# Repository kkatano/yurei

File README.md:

# Yurei
A Tenkeyless PCB inspired by Phantom

## Features
 * QMK Firmware
 * Teensy 2.0 controller
 * Minimal layout support
 * No switch LEDs and no underglow
 * All switches are south facing
 * Compatible with Filco Majestouch 2 case
 * Designed with KiCAD 5.1.4

## Supported Layouts
 * ANSI

## Supported Switches
 * Cherry MX and Cherry MX style switches

## Supported Cases
 * Filco Majestouch 2

### Note
 * [A bit modification to Filco case](images/bottom-case-mod.png) is required to install the USB cable.
 * Some other keyboard cases may also be compatible, but they have not been tested.
 * [YMDK aluminum case is not compatible](images/filco-pcb-and-ymdk-case-problem.pdf) (almost good but plate and pcb are slightly too thick, so that it causes a gap between the top and bottom cases).
   * Genuine filco PCBs and phantom PCBs also have the same problem.
   * I'm designing a new concept PCB named [Wallaby](https://github.com/kkatano/wallaby) to solve this problem. 

## BOM

| Reference | Description | Value     |URL                                                                                                      | Qty | 
|-----------|-------------|-----------|---------------------------------------------------------------------------------------------------------|-----| 
| D1-D87    | Diode       | 1N4148    |https://www.digikey.jp/product-detail/en/on-semiconductor/1N4148/1N4148FS-ND/458603                      | 87  | 
| L1, L2    | LED         | LED       |https://www.digikey.jp/product-detail/en/vishay-semiconductor-opto-division/VLHW4100/751-1502-ND/2403143 | 2   | 
| R1, R2    | Resistor    | 10k       |https://www.digikey.jp/product-detail/en/yageo/MFR-25FBF52-10K/10.0KXBK-ND/13219                         | 2   | 
| SW1-SW87  | Key switch  | Cherry MX |                                                                                                         | 87  | 
| U1        | Controller  | Teensy2.0 |https://www.pjrc.com/store/teensy.html                                                                   | 1   | 

You also need following parts to build keyboard.

 * [LED spacer](https://www.digikey.jp/product-detail/en/keystone-electronics/7362/36-7362-ND/316720)
   * 2 pieces
 * Stabilizers
   * 4 x 2u and 1 x 6.25u
 * Plate
 * Case
 * USB mini-B cable

## Firmware

https://github.com/qmk/qmk_firmware/tree/master/keyboards/yurei

## Lisence

Yurei is released under the MIT License.

## Credits

### [The Phantom](http://bathroomepiphanies.com/keyboards/phantom/)

Source of inspiration.

### Teensy library for KiCAD

Teensy symbol and footprint are based on XenGi's libraries released under the MIT license.

#### [teensy_library](https://github.com/XenGi/teensy_library)

Copyright (c) 2015 Ricardo Band  
https://github.com/XenGi/teensy_library/blob/master/LICENSE 

#### [teensy.pretty](https://github.com/XenGi/teensy.pretty)

Copyright (c) 2015 Ricardo Band  
https://github.com/XenGi/teensy.pretty/blob/master/LICENSE

### [KiCad Libraries](https://kicad-pcb.org/libraries/)

All symbols and footprints except Teensy are based on The KiCad libraries.

### [Keyboard Layouter Plugin](https://github.com/yskoht/keyboard-layouter)

Handy plugin to place the switches.

### [keyboard-layout-editor.com](http://www.keyboard-layout-editor.com/)

Used to generate keyboard layout data to be input to Keyboard Layouter.

### [FreeRouting](https://freerouting.org/)

Good starting point for routing.

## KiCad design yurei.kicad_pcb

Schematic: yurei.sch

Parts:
D1, D2, D3, D4, D5, D6, D7, D8, D9, D10, D11, D12, D13, D14, D15, D16, D17, D18, D19, D20, D21, D22, D23, D24, D25, D26, D27, D28, D29, D30, D31, D32, D33, D34, D35, D36, D37, D38, D39, D40, D41, D42, D43, D44, D45, D46, D47, D48, D49, D50, D51, D52, D53, D54, D55, D56, D57, D58, D59, D60, D61, D62, D63, D64, D65, D66, D67, D68, D69, D70, D71, D72, D73, D74, D75, D76, D77, D78, D79, D80, D81, D82, D83, D84, D85, D86, D87: 1N4148; D_DO-35_SOD27_P7.62mm_Horizontal
L1, L2: LED; LED_D3.0mm
R1, R2: 10k; R_Axial_DIN0207_L6.3mm_D2.5mm_P7.62mm_Horizontal
SW1, SW2, SW3, SW4, SW5, SW6, SW7, SW8, SW9, SW10, SW11, SW12, SW13, SW14, SW15, SW16, SW17, SW18, SW19, SW20, SW21, SW22, SW23, SW24, SW25, SW26, SW27, SW28, SW29, SW31, SW32, SW33, SW35, SW36, SW37, SW38, SW39, SW40, SW41, SW42, SW43, SW44, SW45, SW46, SW48, SW49, SW50, SW52, SW53, SW54, SW55, SW56, SW57, SW58, SW59, SW60, SW61, SW62, SW65, SW66, SW67, SW68, SW69, SW70, SW71, SW72, SW73, SW74, SW76, SW85, SW86, SW87: SW_SPST; SW_Cherry_MX_1.00u_PCB
SW30: SW_SPST; SW_Cherry_MX_2.00u_PCB
SW34, SW47: SW_SPST; SW_Cherry_MX_1.50u_PCB
SW51: SW_SPST; SW_Cherry_MX_1.75u_PCB
SW63, SW64: SW_SPST; SW_Cherry_MX_2.25u_PCB
SW75: SW_SPST; SW_Cherry_MX_2.75u_PCB
SW77, SW78, SW79, SW81, SW82, SW83, SW84: SW_SPST; SW_Cherry_MX_1.25u_PCB
SW80: SW_SPST; SW_Cherry_MX_6.25u_PCB
U1: Teensy2.0_(C); Teensy2.0

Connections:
Col0: SW1.1, SW17.1, SW34.1, SW51.1, SW64.1, SW77.1, U1.13
Col1: SW2.1, SW18.1, SW35.1, SW52.1, SW78.1, U1.12
Col2: SW3.1, SW19.1, SW36.1, SW53.1, SW65.1, SW79.1, U1.11
Col3: SW4.1, SW20.1, SW37.1, SW54.1, SW66.1, U1.17
Col4: SW5.1, SW21.1, SW38.1, SW55.1, SW67.1, U1.7
Col5: SW6.1, SW22.1, SW39.1, SW56.1, SW68.1, U1.30
Col6: SW7.1, SW23.1, SW40.1, SW57.1, SW69.1, SW80.1, U1.28
Col7: SW8.1, SW24.1, SW41.1, SW58.1, SW70.1, U1.27
Col8: SW9.1, SW25.1, SW42.1, SW59.1, SW71.1, U1.26
Col9: SW10.1, SW26.1, SW43.1, SW60.1, SW72.1, U1.25
Col10: SW11.1, SW27.1, SW44.1, SW61.1, SW73.1, SW81.1, U1.24
Col11: SW12.1, SW28.1, SW45.1, SW62.1, SW74.1, SW82.1, U1.23
Col12: SW13.1, SW29.1, SW46.1, SW75.1, SW83.1, U1.19
Col13: SW30.1, SW47.1, SW63.1, SW84.1, U1.18
Col14: SW14.1, SW31.1, SW48.1, SW85.1, U1.8
Col15: SW15.1, SW32.1, SW49.1, SW76.1, SW86.1, U1.9
Col16: SW16.1, SW33.1, SW50.1, SW87.1, U1.10
GND: L1.1, L2.1, U1.1
LED1: R1.1, U1.22
LED2: R2.1, U1.6
unnamed: D1.2, SW1.2
unnamed: D2.2, SW2.2
unnamed: D3.2, SW3.2
unnamed: D4.2, SW4.2
unnamed: D5.2, SW5.2
unnamed: D6.2, SW6.2
unnamed: D7.2, SW7.2
unnamed: D8.2, SW8.2
unnamed: D9.2, SW9.2
unnamed: D10.2, SW10.2
unnamed: D11.2, SW11.2
unnamed: D12.2, SW12.2
unnamed: D13.2, SW13.2
unnamed: D14.2, SW14.2
unnamed: D15.2, SW15.2
unnamed: D16.2, SW16.2
unnamed: D17.2, SW17.2
unnamed: D18.2, SW18.2
unnamed: D19.2, SW19.2
unnamed: D20.2, SW20.2
unnamed: D21.2, SW21.2
unnamed: D22.2, SW22.2
unnamed: D23.2, SW23.2
unnamed: D24.2, SW24.2
unnamed: D25.2, SW25.2
unnamed: D26.2, SW26.2
unnamed: D27.2, SW27.2
unnamed: D28.2, SW28.2
unnamed: D29.2, SW29.2
unnamed: D30.2, SW30.2
unnamed: D31.2, SW31.2
unnamed: D32.2, SW32.2
unnamed: D33.2, SW33.2
unnamed: D34.2, SW34.2
unnamed: D35.2, SW35.2
unnamed: D36.2, SW36.2
unnamed: D37.2 (A), SW37.2
unnamed: D38.2, SW38.2
unnamed: D39.2, SW39.2
unnamed: D40.2, SW40.2
unnamed: D41.2, SW41.2
unnamed: D42.2, SW42.2
unnamed: D43.2, SW43.2
unnamed: D44.2, SW44.2
unnamed: D45.2, SW45.2
unnamed: D46.2, SW46.2
unnamed: D47.2, SW47.2
unnamed: D48.2, SW48.2
unnamed: D49.2, SW49.2
unnamed: D50.2, SW50.2
unnamed: D51.2, SW51.2
unnamed: D52.2, SW52.2
unnamed: D53.2, SW53.2
unnamed: D54.2, SW54.2
unnamed: D55.2, SW55.2
unnamed: D56.2, SW56.2
unnamed: D57.2, SW57.2
unnamed: D58.2, SW58.2
unnamed: D59.2, SW59.2
unnamed: D60.2, SW60.2
unnamed: D61.2, SW61.2
unnamed: D62.2, SW62.2
unnamed: D63.2, SW63.2
unnamed: D64.2, SW64.2
unnamed: D65.2, SW65.2
unnamed: D66.2, SW66.2
unnamed: D67.2, SW67.2
unnamed: D68.2, SW68.2
unnamed: D69.2, SW69.2
unnamed: D70.2, SW70.2
unnamed: D71.2, SW71.2
unnamed: D72.2, SW72.2
unnamed: D73.2, SW73.2
unnamed: D74.2, SW74.2
unnamed: D75.2, SW75.2
unnamed: D76.2, SW76.2
unnamed: D77.2, SW77.2
unnamed: D78.2, SW78.2
unnamed: D79.2, SW79.2
unnamed: D80.2, SW80.2
unnamed: D81.2, SW81.2
unnamed: D82.2, SW82.2
unnamed: D83.2, SW83.2
unnamed: D84.2, SW84.2
unnamed: D85.2, SW85.2
unnamed: D86.2, SW86.2
unnamed: D87.2, SW87.2
unnamed: L1.2, R1.2
unnamed: L2.2, R2.2
Row0: D1.1, D2.1, D3.1, D4.1, D5.1, D6.1, D7.1, D8.1, D9.1, D10.1, D11.1, D12.1, D13.1, D14.1, D15.1, D16.1, U1.21
Row1: D17.1, D18.1, D19.1, D20.1, D21.1, D22.1, D23.1, D24.1, D25.1, D26.1, D27.1, D28.1, D29.1, D30.1, D31.1, D32.1, D33.1, U1.20
Row2: D34.1, D35.1, D36.1, D37.1 (K), D38.1, D39.1, D40.1, D41.1, D42.1, D43.1, D44.1, D45.1, D46.1, D47.1, D48.1, D49.1, D50.1, U1.5
Row3: D51.1, D52.1, D53.1, D54.1, D55.1, D56.1, D57.1, D58.1, D59.1, D60.1, D61.1, D62.1, D63.1, U1.4
Row4: D64.1, D65.1, D66.1, D67.1, D68.1, D69.1, D70.1, D71.1, D72.1, D73.1, D74.1, D75.1, D76.1, U1.3
Row5: D77.1, D78.1, D79.1, D80.1, D81.1, D82.1, D83.1, D84.1, D85.1, D86.1, D87.1, U1.2

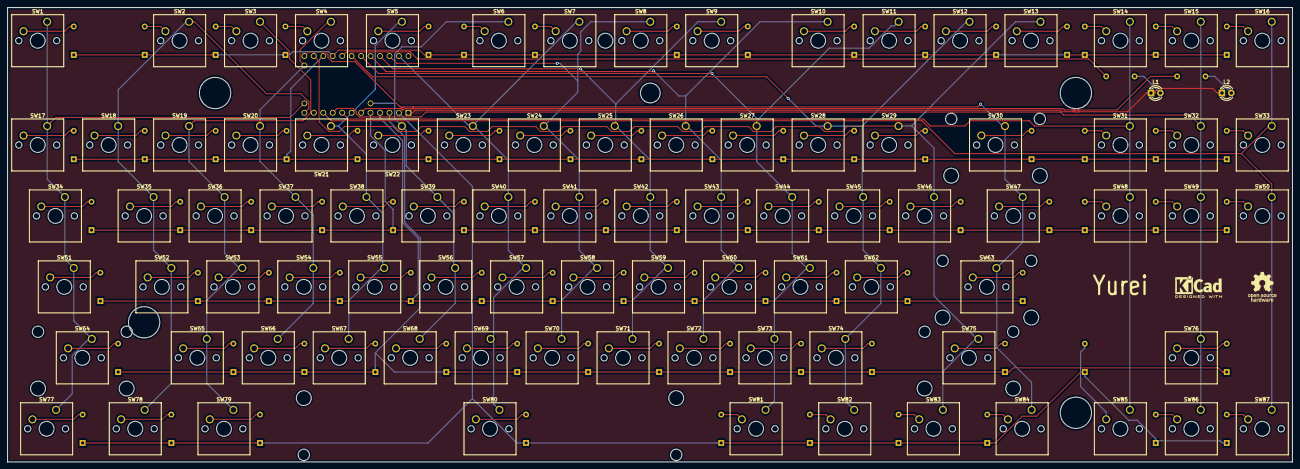
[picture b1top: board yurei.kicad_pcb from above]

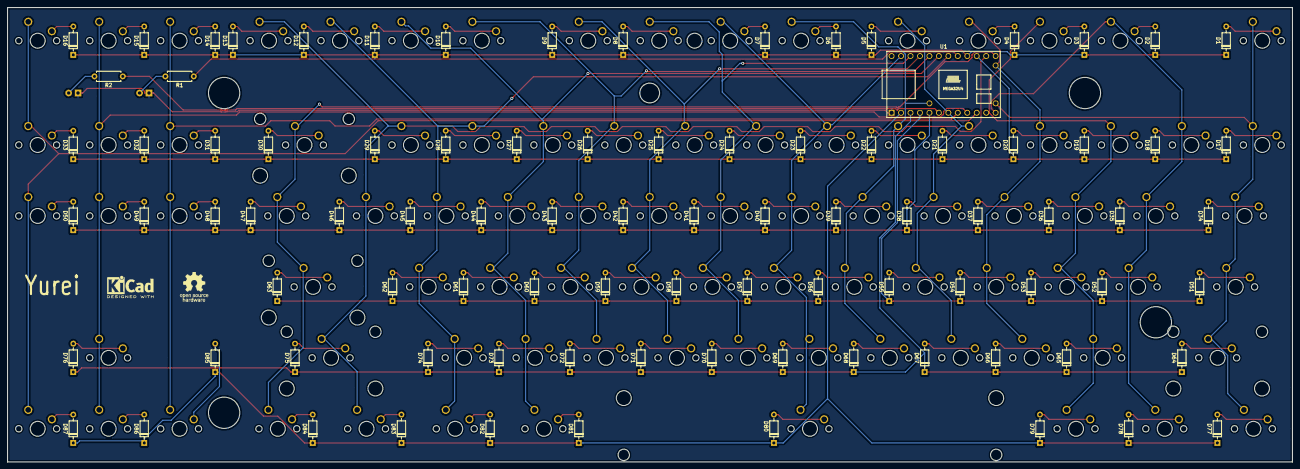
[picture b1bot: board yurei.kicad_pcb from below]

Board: 2 copper layers, 344.8 x 121.9 mm, 183 parts (92 on the bottom side), 115 nets.

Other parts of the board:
kicad1, kicad2: KiCad-Logo2_5mm_SilkScreen
oshw1, oshw2: OSHW-Logo_7.5x8mm_SilkScreen

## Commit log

2019-11-09 Initialize project
2019-11-09 Add teensy library
2019-11-12 Drafting PCB
2019-11-14 Routed
2019-11-16 Create gerber files
2019-11-16 Remove files to be ignored
2020-01-11 Clean up
2020-01-11 Add logo to PCB
2020-01-11 Update footprint
2020-01-11 Update footprints
2020-01-11 Update route
2020-01-12 pdate README.md
2020-01-18 Update image
2020-01-18 Update BOM
2020-01-18 Update URL
2020-01-18 Add case mod picture
